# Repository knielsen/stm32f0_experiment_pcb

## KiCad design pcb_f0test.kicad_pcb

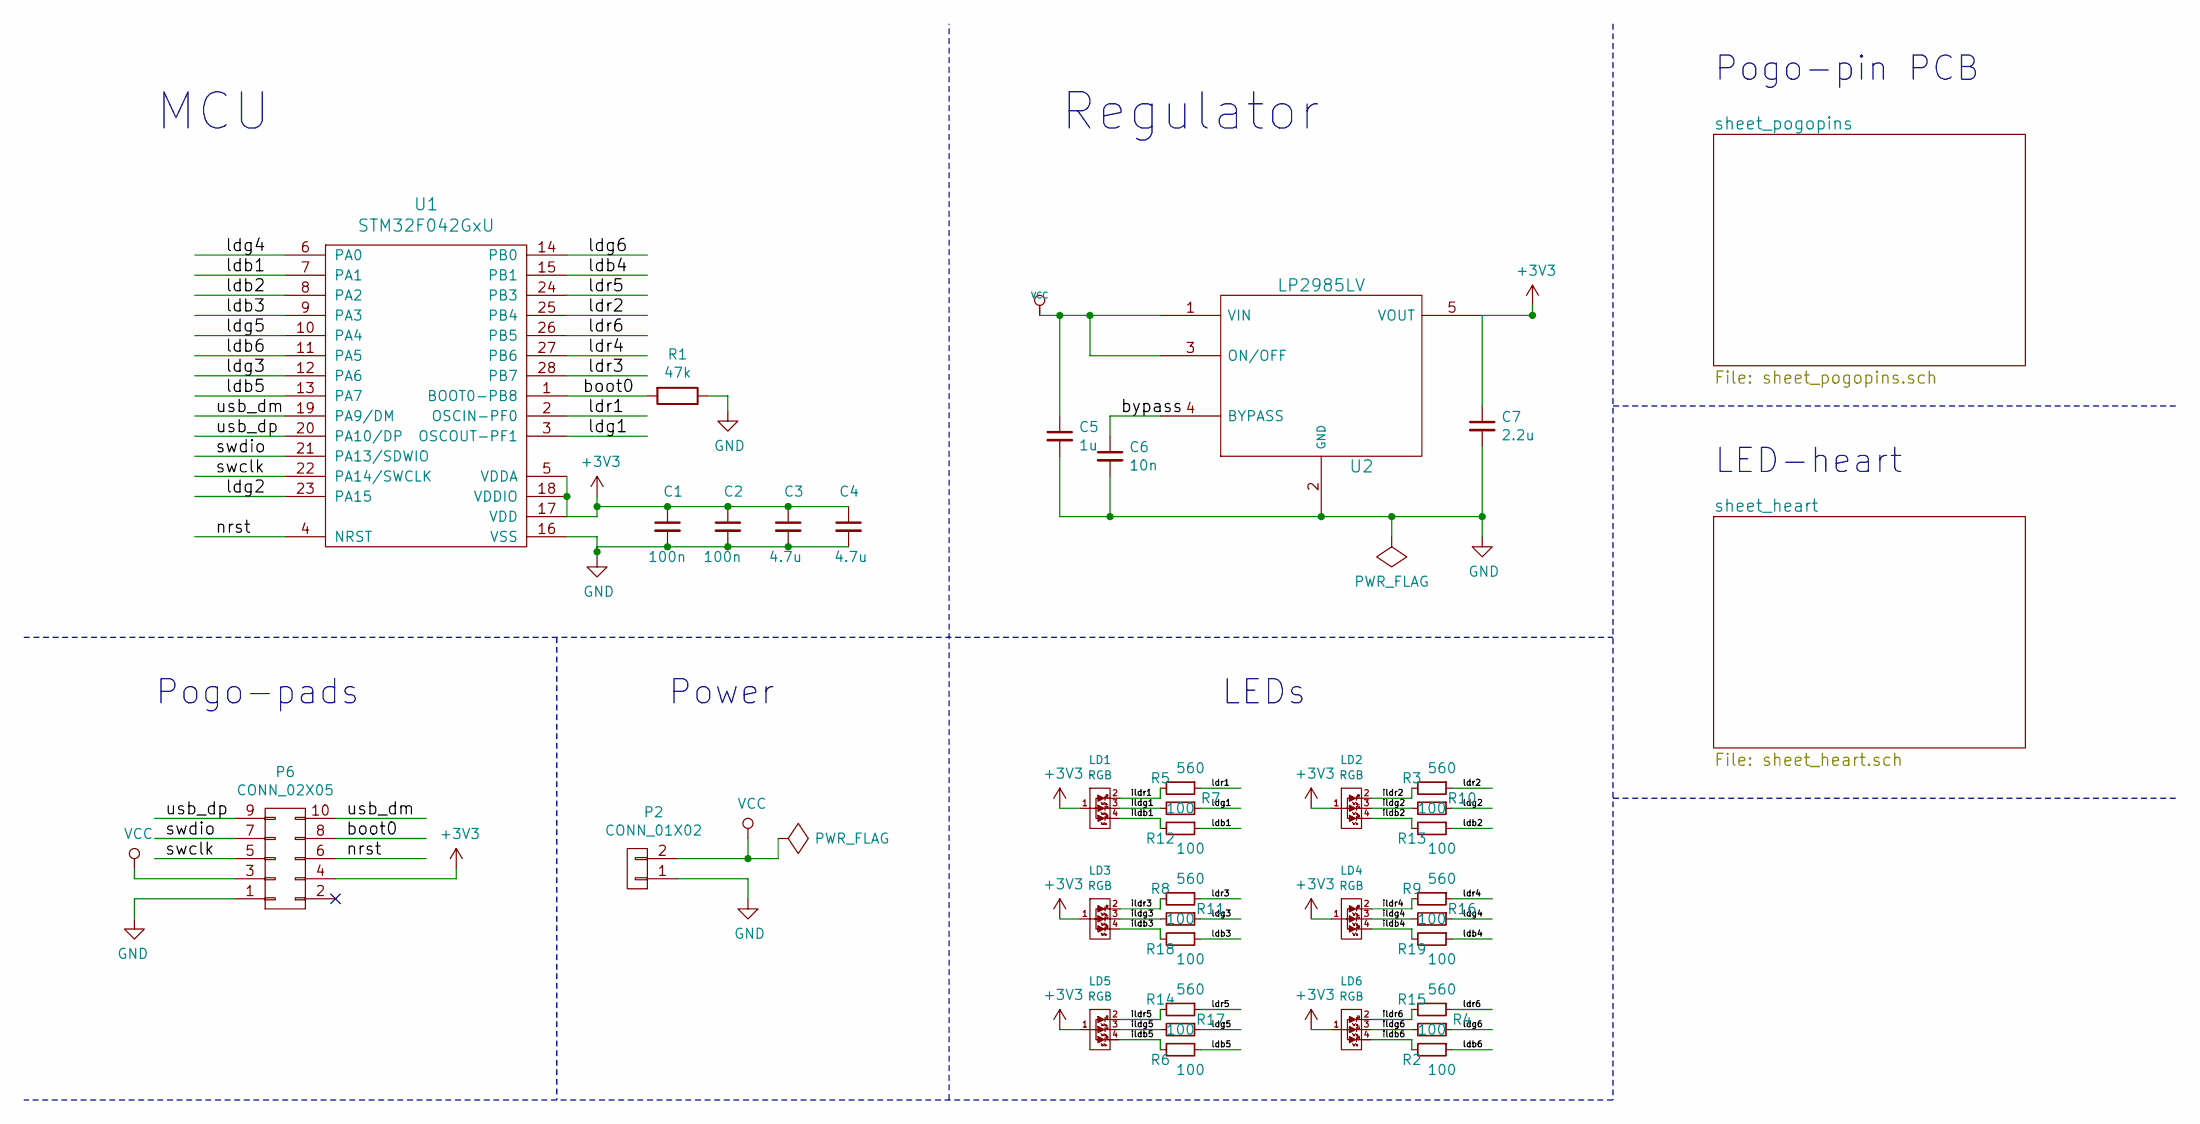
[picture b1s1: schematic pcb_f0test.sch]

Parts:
C1, C2: 100n; C_0603
C3, C4: 4.7u; C_0603
C5: 1u; C_0603
C6: 10n; C_0603
C7: 2.2u; C_0603
LD1, LD2, LD3, LD4, LD5, LD6: RGB; RGB_0603_ALTPINOUT
P2: CONN_01X02; Pin_Header_Straight_1x02
P6: CONN_02X05; pogopads_2x5_50mil_smd
R1: 47k; R_0603
R2, R4, R6, R7, R10, R11, R12, R13, R16, R17, R18, R19: 100; R_0603
R3, R5, R8, R9, R14, R15: 560; R_0603
U1: STM32F042GxU; UFQFPN28_fixpad
U2: LP2985LV; SOT-23-5

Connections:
+3V3: C1.1, C2.1, C3.1, C4.1, C7.1, LD1.1 (AG), LD2.1 (AG), LD3.1 (AG), LD4.1 (AG), LD5.1 (AG), LD6.1 (AG), P6.4, U1.5 (VDDA), U1.17 (VDD), U1.18 (VDDIO), U2.5 (VOUT)
/boot0: P6.8, R1.2, U1.1 (BOOT0-PB8)
/bypass: C6.1, U2.4 (BYPASS)
/ildb1: LD1.4 (R), R12.2
/ildb2: LD2.4 (R), R13.2
/ildb3: LD3.4 (R), R18.2
/ildb4: LD4.4 (R), R19.2
/ildb5: LD5.4 (R), R6.2
/ildb6: LD6.4 (R), R2.2
/ildg1: LD1.3 (R), R7.2
/ildg2: LD2.3 (R), R10.2
/ildg3: LD3.3 (R), R11.2
/ildg4: LD4.3 (R), R16.2
/ildg5: LD5.3 (R), R17.2
/ildg6: LD6.3 (R), R4.2
/ildr1: LD1.2 (R), R5.2
/ildr2: LD2.2 (R), R3.2
/ildr3: LD3.2 (R), R8.2
/ildr4: LD4.2 (R), R9.2
/ildr5: LD5.2 (R), R14.2
/ildr6: LD6.2 (R), R15.2
/ldb1: R12.1, U1.7 (PA1)
/ldb2: R13.1, U1.8 (PA2)
/ldb3: R18.1, U1.9 (PA3)
/ldb4: R19.1, U1.15 (PB1)
/ldb5: R6.1, U1.13 (PA7)
/ldb6: R2.1, U1.11 (PA5)
/ldg1: R7.1, U1.3 (OSCOUT-PF1)
/ldg2: R10.1, U1.23 (PA15)
/ldg3: R11.1, U1.12 (PA6)
/ldg4: R16.1, U1.6 (PA0)
/ldg5: R17.1, U1.10 (PA4)
/ldg6: R4.1, U1.14 (PB0)
/ldr1: R5.1, U1.2 (OSCIN-PF0)
/ldr2: R3.1, U1.25 (PB4)
/ldr3: R8.1, U1.28 (PB7)
/ldr4: R9.1, U1.27 (PB6)
/ldr5: R14.1, U1.24 (PB3)
/ldr6: R15.1, U1.26 (PB5)
/nrst: P6.6, U1.4 (NRST)
/swclk: P6.5, U1.22 (PA14/SWCLK)
/swdio: P6.7, U1.21 (PA13/SDWIO)
/usb_dm: P6.10, U1.19 (PA9/DM)
/usb_dp: P6.9, U1.20 (PA10/DP)
GND: C1.2, C2.2, C3.2, C4.2, C5.2, C6.2, C7.2, P2.1, P6.1, R1.1, U1.16 (VSS), U2.2 (GND)
VCC: C5.1, P2.2, P6.3, U2.1 (VIN), U2.3 (ON/OFF)

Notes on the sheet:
Pogo-pads
Power
LEDs
MCU
Regulator
Pogo-pin PCB
LED-heart

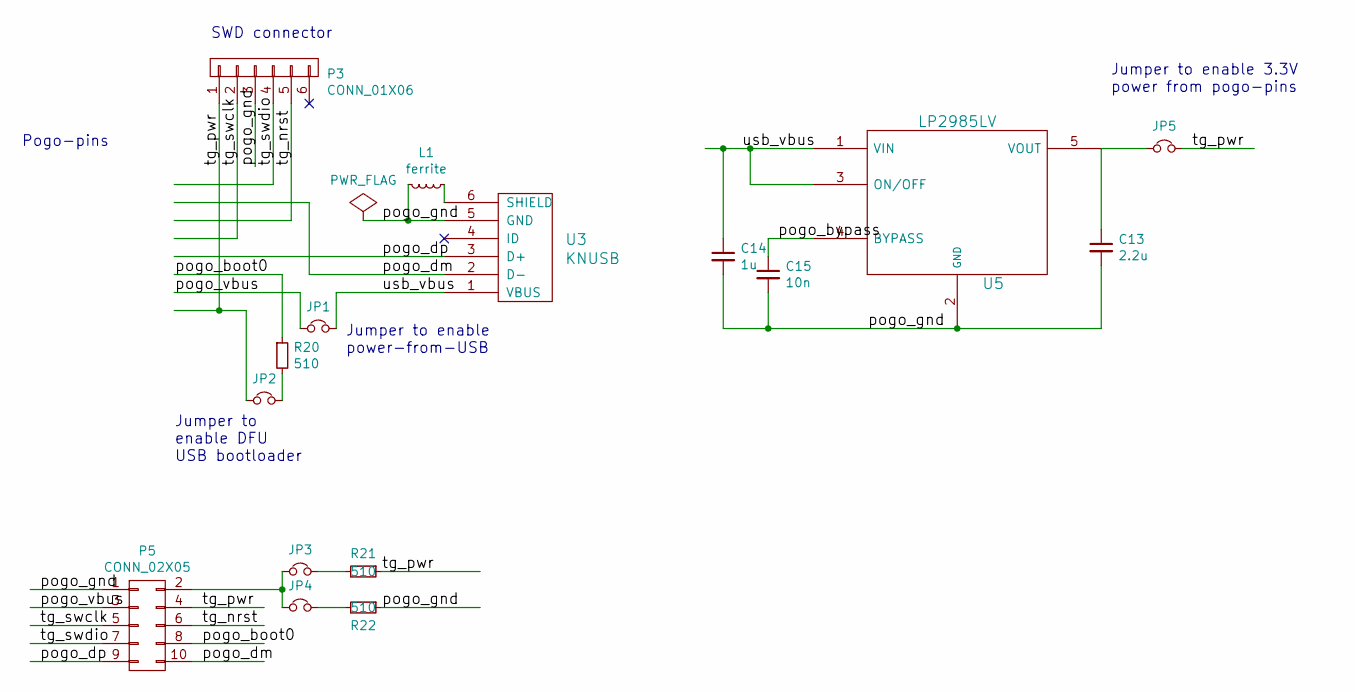
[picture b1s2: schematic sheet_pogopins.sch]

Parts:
C13: 2.2u; C_0603
C14: 1u; C_0603
C15: 10n; C_0603
JP1, JP2, JP3, JP4, JP5: Jumper_NC_Small; Pin_Header_Straight_1x02
L1: ferrite; R_0603_HandSoldering
P3: CONN_01X06; Pin_Header_Straight_1x06
P5: CONN_02X05; pogopins_2x5_50mil
R20, R21, R22: 510; R_0603
U3: KNUSB; 10103594-0001LF
U5: LP2985LV; SOT-23-5

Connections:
/sheet_pogopins/pogo_boot0: P5.8, R20.1
/sheet_pogopins/pogo_bypass: C15.1, U5.4 (BYPASS)
/sheet_pogopins/pogo_dm: P5.10, U3.2 (D-)
/sheet_pogopins/pogo_dp: P5.9, U3.3 (D+)
/sheet_pogopins/pogo_gnd: C13.2, C14.2, C15.2, L1.2, P3.3, P5.1, R22.1, U3.5 (GND), U5.2 (GND)
/sheet_pogopins/pogo_vbus: JP1.2, P5.3
/sheet_pogopins/tg_nrst: P3.5, P5.6
/sheet_pogopins/tg_pwr: JP2.1, JP5.2, P3.1, P5.4, R21.1
/sheet_pogopins/tg_swclk: P3.2, P5.5
/sheet_pogopins/tg_swdio: P3.4, P5.7
/sheet_pogopins/usb_vbus: C14.1, JP1.1, U3.1 (VBUS), U5.1 (VIN), U5.3 (ON/OFF)
unnamed: C13.1, JP5.1, U5.5 (VOUT)
unnamed: JP2.2, R20.2
unnamed: JP3.1, R21.2
unnamed: JP3.2, JP4.2, P5.2
unnamed: JP4.1, R22.2
unnamed: L1.1, U3.6 (SHIELD)

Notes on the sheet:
Jumper to enable DFU USB bootloader
Jumper to enable power-from-USB
SWD connector
Pogo-pins
Jumper to enable 3.3V power from pogo-pins

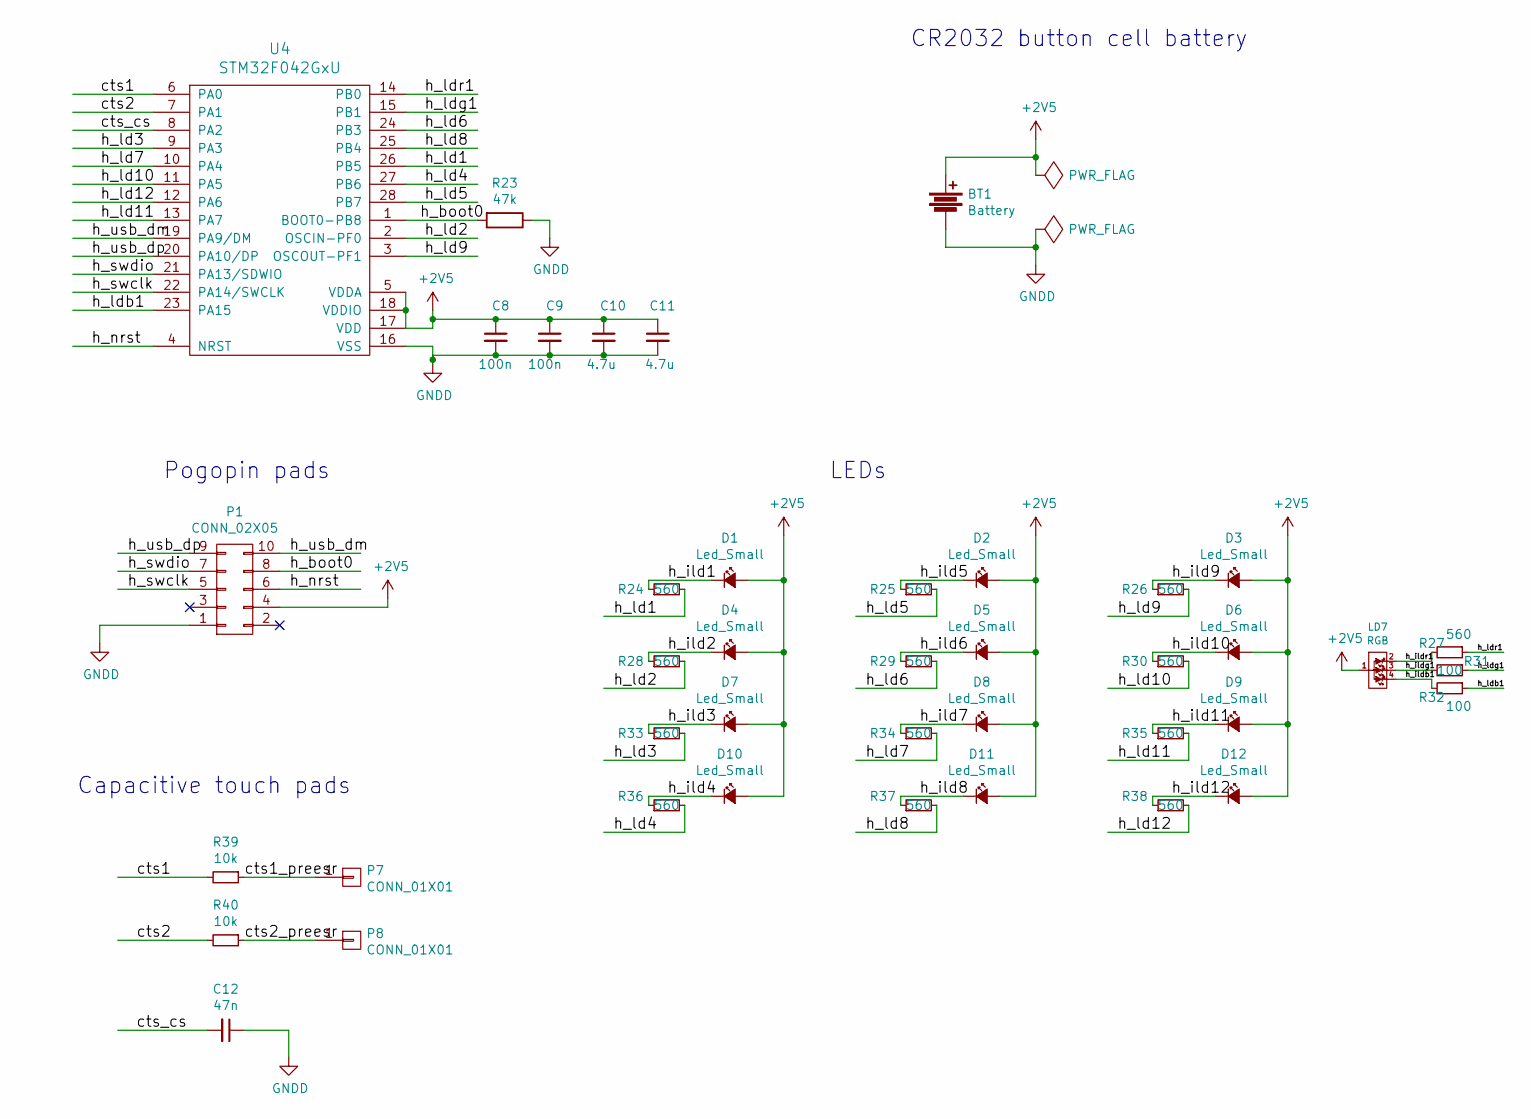
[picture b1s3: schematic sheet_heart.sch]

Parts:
BT1: Battery; Linx_BAT_HLD_001
C8, C9: 100n; C_0603
C10, C11: 4.7u; C_0603
C12: 47n; C_0603
D1, D2, D3, D4, D5, D6, D7, D8, D9, D10, D11, D12: Led_Small; LED_0603
LD7: RGB; RGB_0603_ALTPINOUT
P1: CONN_02X05; pogopads_2x5_50mil_smd
P7, P8: CONN_01X01; Touchpad_8mm
R23: 47k; R_0603
R24, R25, R26, R27, R28, R29, R30, R33, R34, R35, R36, R37, R38: 560; R_0603
R31, R32: 100; R_0603
R39, R40: 10k; R_0603
U4: STM32F042GxU; UFQFPN28_fixpad

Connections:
+2V5: BT1.1, C8.1, C9.1, C10.1, C11.1, D1.2 (A), D2.2 (A), D3.2 (A), D4.2 (A), D5.2 (A), D6.2 (A), D7.2 (A), D8.2 (A), D9.2 (A), D10.2 (A), D11.2 (A), D12.2 (A), LD7.1 (AG), P1.4, U4.5 (VDDA), U4.17 (VDD), U4.18 (VDDIO)
/sheet_heart/cts1: R39.2, U4.6 (PA0)
/sheet_heart/cts1_preesr: P7.1, R39.1
/sheet_heart/cts2: R40.2, U4.7 (PA1)
/sheet_heart/cts2_preesr: P8.1, R40.1
/sheet_heart/cts_cs: C12.2, U4.8 (PA2)
/sheet_heart/h_boot0: P1.8, R23.2, U4.1 (BOOT0-PB8)
/sheet_heart/h_ild1: D1.1 (K), R24.1
/sheet_heart/h_ild2: D4.1 (K), R28.1
/sheet_heart/h_ild3: D7.1 (K), R33.1
/sheet_heart/h_ild4: D10.1 (K), R36.1
/sheet_heart/h_ild5: D2.1 (K), R25.1
/sheet_heart/h_ild6: D5.1 (K), R29.1
/sheet_heart/h_ild7: D8.1 (K), R34.1
/sheet_heart/h_ild8: D11.1 (K), R37.1
/sheet_heart/h_ild9: D3.1 (K), R26.1
/sheet_heart/h_ild10: D6.1 (K), R30.1
/sheet_heart/h_ild11: D9.1 (K), R35.1
/sheet_heart/h_ild12: D12.1 (K), R38.1
/sheet_heart/h_ildb1: LD7.4 (R), R32.2
/sheet_heart/h_ildg1: LD7.3 (R), R31.2
/sheet_heart/h_ildr1: LD7.2 (R), R27.2
/sheet_heart/h_ld1: R24.2, U4.26 (PB5)
/sheet_heart/h_ld2: R28.2, U4.2 (OSCIN-PF0)
/sheet_heart/h_ld3: R33.2, U4.9 (PA3)
/sheet_heart/h_ld4: R36.2, U4.27 (PB6)
/sheet_heart/h_ld5: R25.2, U4.28 (PB7)
/sheet_heart/h_ld6: R29.2, U4.24 (PB3)
/sheet_heart/h_ld7: R34.2, U4.10 (PA4)
/sheet_heart/h_ld8: R37.2, U4.25 (PB4)
/sheet_heart/h_ld9: R26.2, U4.3 (OSCOUT-PF1)
/sheet_heart/h_ld10: R30.2, U4.11 (PA5)
/sheet_heart/h_ld11: R35.2, U4.13 (PA7)
/sheet_heart/h_ld12: R38.2, U4.12 (PA6)
/sheet_heart/h_ldb1: R32.1, U4.23 (PA15)
/sheet_heart/h_ldg1: R31.1, U4.15 (PB1)
/sheet_heart/h_ldr1: R27.1, U4.14 (PB0)
/sheet_heart/h_nrst: P1.6, U4.4 (NRST)
/sheet_heart/h_swclk: P1.5, U4.22 (PA14/SWCLK)
/sheet_heart/h_swdio: P1.7, U4.21 (PA13/SDWIO)
/sheet_heart/h_usb_dm: P1.10, U4.19 (PA9/DM)
/sheet_heart/h_usb_dp: P1.9, U4.20 (PA10/DP)
GNDD: BT1.2, C8.2, C9.2, C10.2, C11.2, C12.1, P1.1, R23.1, U4.16 (VSS)

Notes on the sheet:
Capacitive touch pads
CR2032 button cell battery
Pogopin pads
LEDs

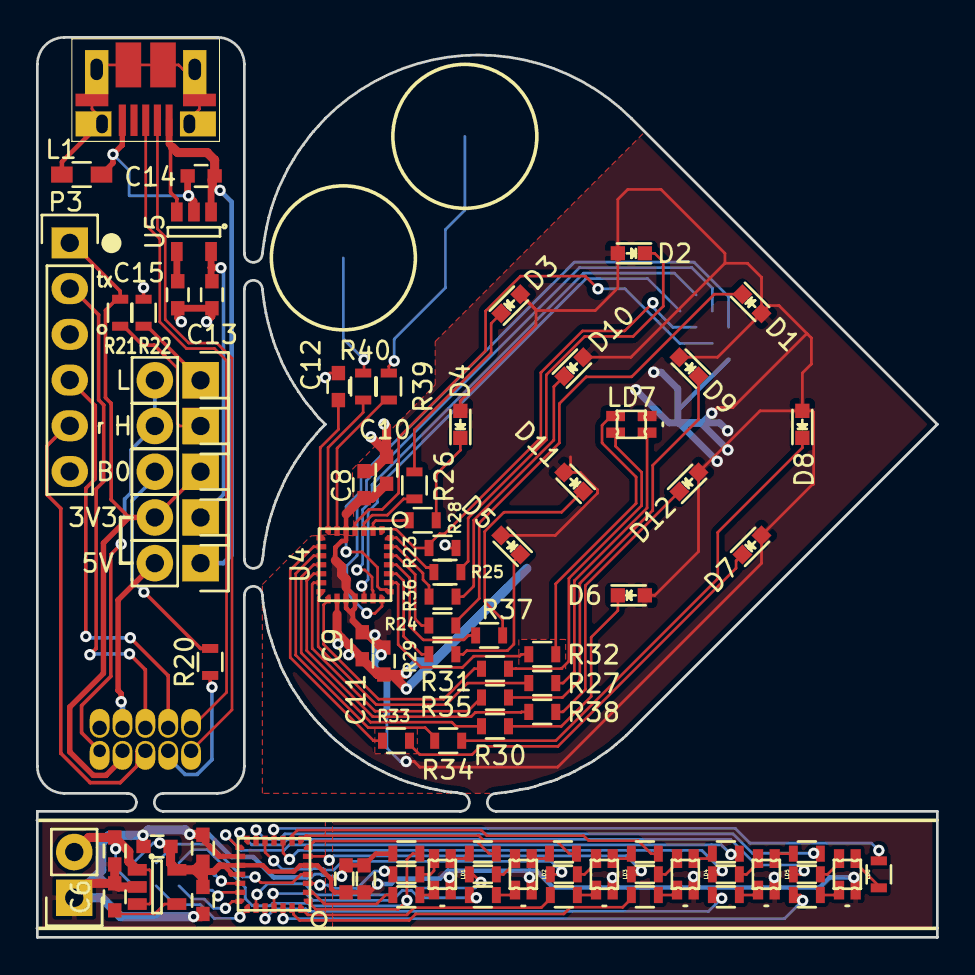
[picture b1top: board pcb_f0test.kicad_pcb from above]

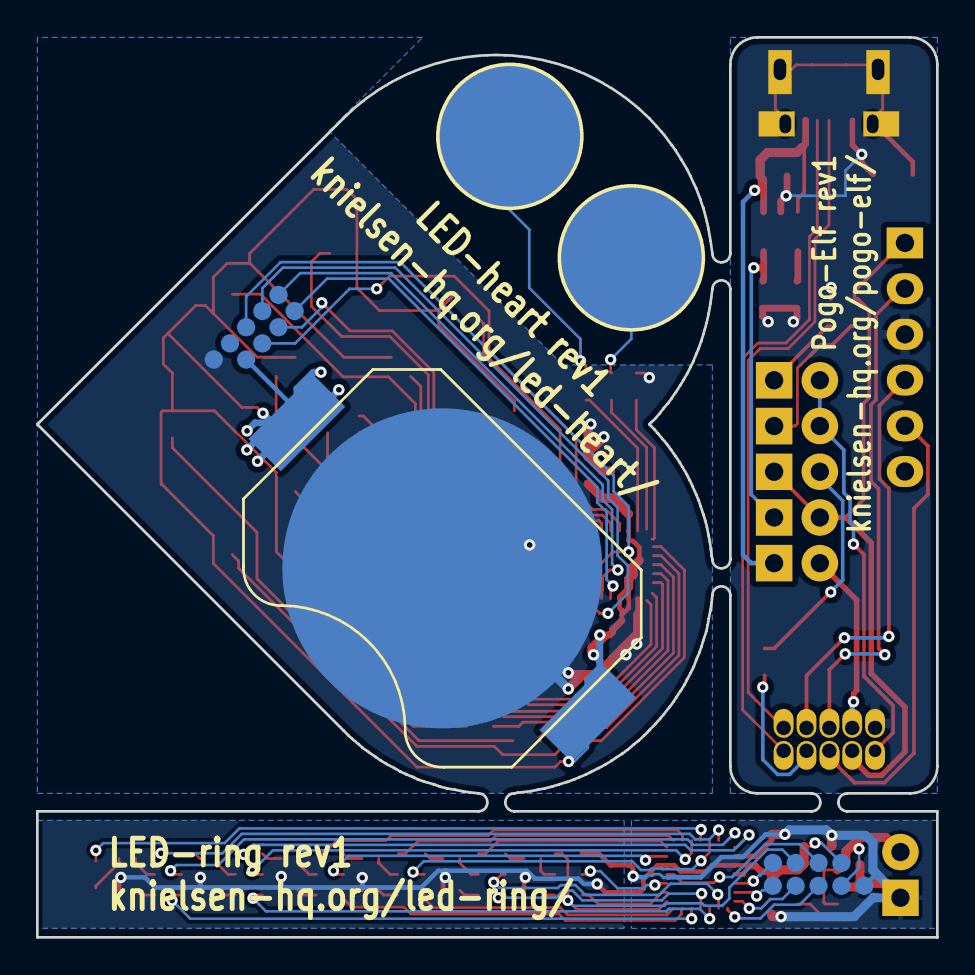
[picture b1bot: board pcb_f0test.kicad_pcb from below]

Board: 2 copper layers, 50.0 x 50.0 mm, 93 parts (5 on the bottom side), 106 nets.

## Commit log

2016-06-22 Initial routing; still needs to be tweaked a bit.
2016-06-22 Fairly good routing now.
2016-06-24 Some misc. changes.
2016-06-26 Fix corner pads on QFN.
2016-06-26 Fix numbering of LEDs.
2016-06-29 Add pogopin board, fixing pogopad layout.
2016-07-04 Initial stab at a "christmas heart" decoration pcb.
2016-07-05 Fix PCB outline (might still need a bit of tweaks for the ring).
2016-07-05 Improved routing of the heart.
2016-07-06 Routing cleanup and silkscreen on heart.
2016-07-07 Add .gitignore
2016-07-07 Tweak outline of ring PCB.
2016-07-07 New routing of pogo-pins board (still needs some cleanup).
2016-07-08 Cleanup routing on pogo-pins pcb, looks good now.
2016-07-08 Silkscreen and cleanup.
2016-07-08 More silk screen, getting pretty close now, I think.
2016-07-16 Only minor changes, if any.
2016-07-16 Switch RGB LED on heart PCB to new type/pinout.
2016-07-17 Change RGB LED footprint to match new batch of cheap 0603.
2016-07-26 Final gerbers for rev1.
